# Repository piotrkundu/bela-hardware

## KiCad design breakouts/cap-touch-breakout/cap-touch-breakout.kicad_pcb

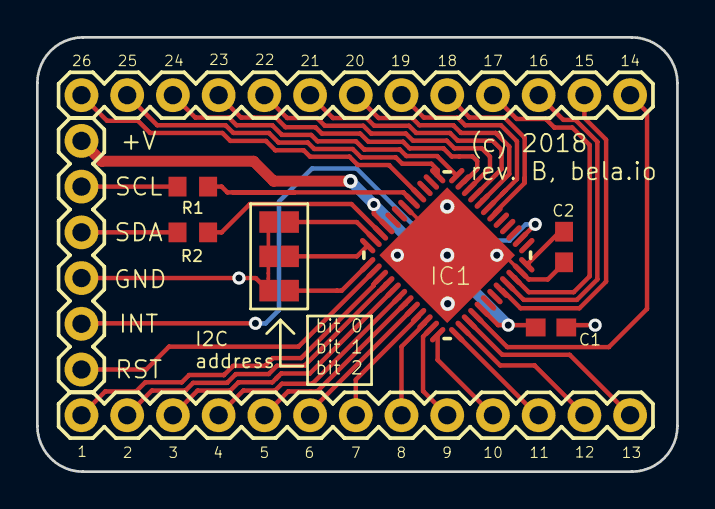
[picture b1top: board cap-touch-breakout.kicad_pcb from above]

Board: 2 copper layers, 35.6 x 24.1 mm, 11 parts (0 on the bottom side), 38 nets.

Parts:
C1, C2: C-USC0603; C0603
IC1: CY8C206X6A; QFN48-LEADS
JP1: M06SILK_FEMALE_PTH; 1X06
JP3, JP4: M13; 1X13
R1, R2: R-EU_R0603; R0603
U$2, U$3, U$4: SOLDER_JUMPER

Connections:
/EVENT: IC1.2, JP1.5
/I2C_SCL: JP1.2, R1.2
/I2C_SDA: JP1.3, R2.2
/XRES: IC1.26, JP1.6
GND: C1.1, C2.2, IC1.18, IC1.47, IC1.EXP, JP1.4, U$2.P$2, U$3.P$2, U$4.P$2
unnamed: C2.1, IC1.48
unnamed: IC1.6, JP3.5
unnamed: IC1.7, JP3.6
unnamed: IC1.8, JP3.7
unnamed: IC1.9, JP3.8
unnamed: IC1.10, JP3.9
unnamed: IC1.11, JP3.10
unnamed: IC1.12, JP3.11
unnamed: IC1.13, JP3.12
unnamed: IC1.16, JP3.13
unnamed: IC1.17, R1.1
unnamed: IC1.22, R2.1
unnamed: IC1.23, U$2.P$1
unnamed: IC1.24, U$3.P$1
unnamed: IC1.25, U$4.P$1
unnamed: IC1.27, JP4.1
unnamed: IC1.28, JP4.2
unnamed: IC1.29, JP4.3
unnamed: IC1.30, JP4.4
unnamed: IC1.31, JP4.5
unnamed: IC1.32, JP4.6
unnamed: IC1.33, JP4.7
unnamed: IC1.34, JP4.8
unnamed: IC1.35, JP4.9
unnamed: IC1.36, JP4.10
unnamed: IC1.37, JP4.11
unnamed: IC1.38, JP4.12
unnamed: IC1.39, JP4.13
unnamed: IC1.40, JP3.1
unnamed: IC1.44, JP3.2
unnamed: IC1.45, JP3.3
unnamed: IC1.46, JP3.4
VCC: C1.2, IC1.21, IC1.41, JP1.1

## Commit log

2018-12-13 Added Kicad design files for CapTouch breakout boards
2018-12-13 Modified readme to also include Kicad as cad software used for the designs
2019-05-15 Rev. B3 of the Bela Mini cape adds resistors R6 and R7 to reduce the noise when the audio output is driving a DI box and the codec is not active.
2019-12-09 Added rev. B3 of the Bela cape

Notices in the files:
breakouts/cap-touch-breakout/cap-touch-breakout.kicad_pcb:
(c) 2018
